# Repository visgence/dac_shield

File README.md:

Arduino DAC Shield
2013 Visgence Inc

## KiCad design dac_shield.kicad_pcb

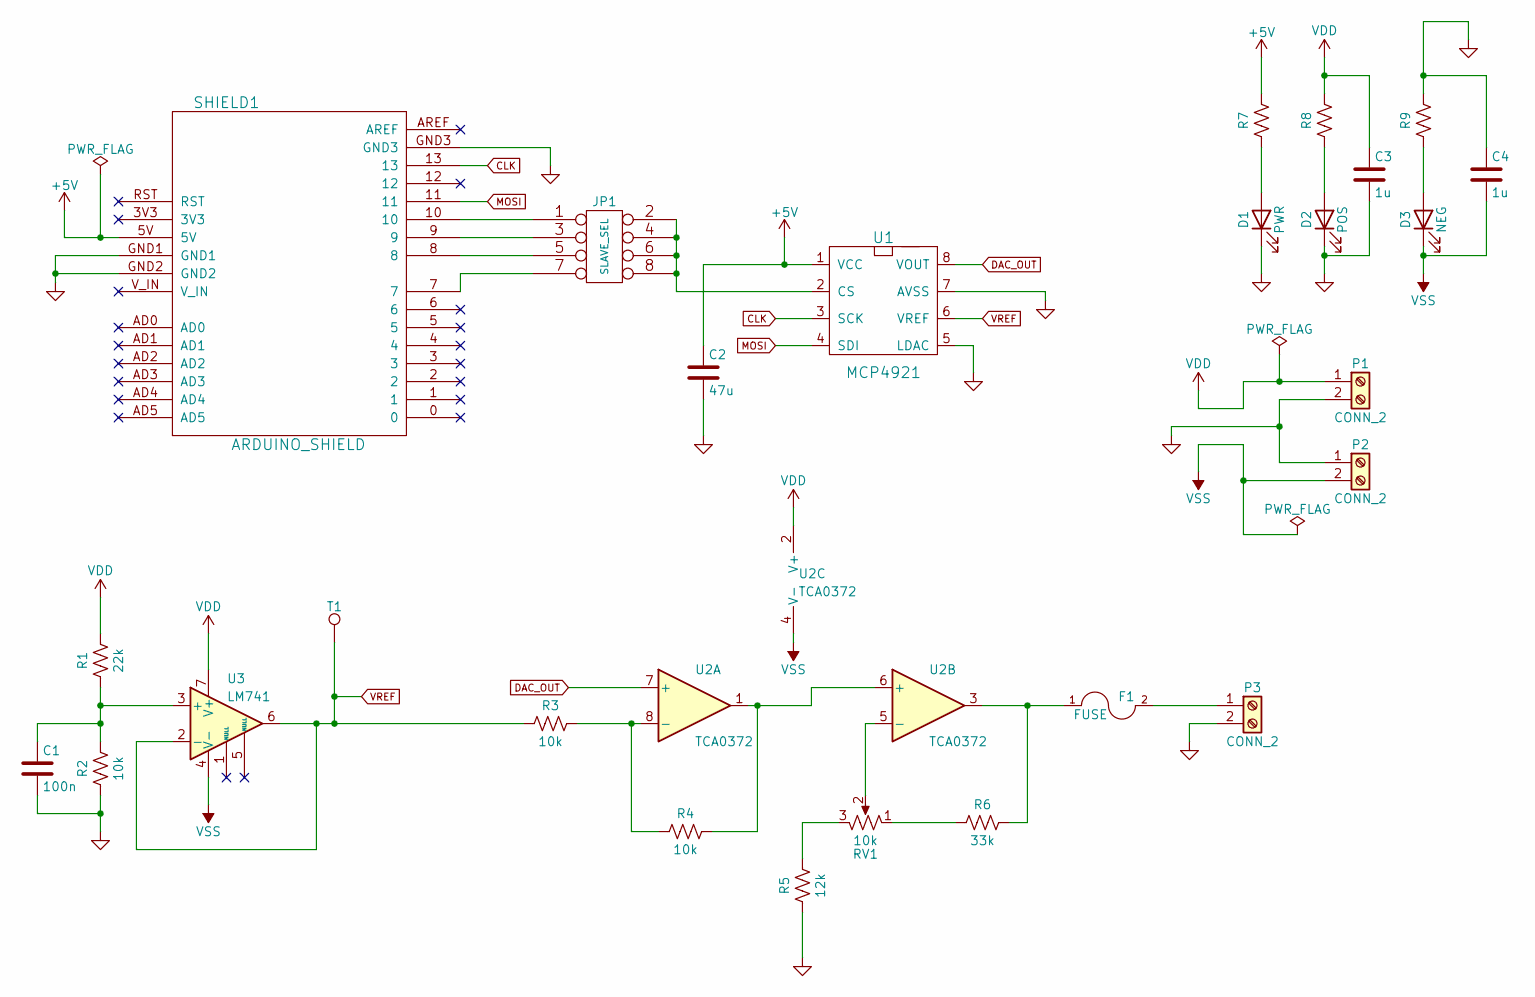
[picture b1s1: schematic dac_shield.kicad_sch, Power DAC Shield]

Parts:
C1: 100n; SM1206_VIS
C2: 47u; SM1206POL_VIS
C3, C4: 1u; SM1206_VIS
D1: PWR; LED_0603_1608Metric
D2: POS; LED_0603_1608Metric
D3: NEG; LED_0603_1608Metric
F1: FUSE; SM1210L
JP1: SLAVE_SEL; pin_array_4x2
P1, P2, P3: CONN_2; bornier2
R1: 22k; R_0603_1608Metric
R2, R3, R4: 10k; R_0603_1608Metric
R5: 12k; R_0603_1608Metric
R6: 33k; R_0603_1608Metric
R7, R8, R9: R_0603_1608Metric
RV1: 10k; Var_resistor
SHIELD1: ARDUINO_SHIELD; ARDUINO_SHIELD_2_040pins
T1: VrefTest; PINTST
U1: MCP4921; DIP-8__300_ELL
U2: TCA0372; DIP-8__300_ELL
U3: LM741; DIP-8__300_ELL

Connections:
+5V: C2.1, R7.2, SHIELD1.5V, U1.1 (VCC)
CLK: SHIELD1.13, U1.3 (SCK)
DAC_OUT: U1.8 (VOUT), U2.7 (+)
GND: C1.2, C2.2, C3.2, C4.1, D1.1 (K), D2.1 (K), P1.2, P2.1, P3.2, R2.1, R5.1, R9.2, SHIELD1.GND1, SHIELD1.GND2, SHIELD1.GND3, U1.5 (LDAC), U1.7 (AVSS)
MOSI: SHIELD1.11, U1.4 (SDI)
unnamed: C1.1, R1.1, R2.2, U3.3 (+)
unnamed: D1.2 (A), R7.1
unnamed: D2.2 (A), R8.1
unnamed: D3.2 (A), R9.1
unnamed: F1.1, R6.2, U2.3
unnamed: F1.2, P3.1
unnamed: JP1.1, SHIELD1.10
unnamed: JP1.2, JP1.4, JP1.6, JP1.8, U1.2 (CS)
unnamed: JP1.3, SHIELD1.9
unnamed: JP1.5, SHIELD1.8
unnamed: JP1.7, SHIELD1.7
unnamed: R3.2, R4.1, U2.8 (-)
unnamed: R4.2, U2.1, U2.6 (+)
unnamed: R5.2, RV1.3
unnamed: R6.1, RV1.1
unnamed: RV1.2, U2.5 (-)
VDD: C3.1, P1.1, R1.2, R8.2, U2.2 (V+), U3.7 (V+)
VREF: R3.1, T1.1, U1.6 (VREF), U3.2 (-), U3.6
VSS: C4.2, D3.1 (K), P2.2, U2.4 (V-), U3.4 (V-)

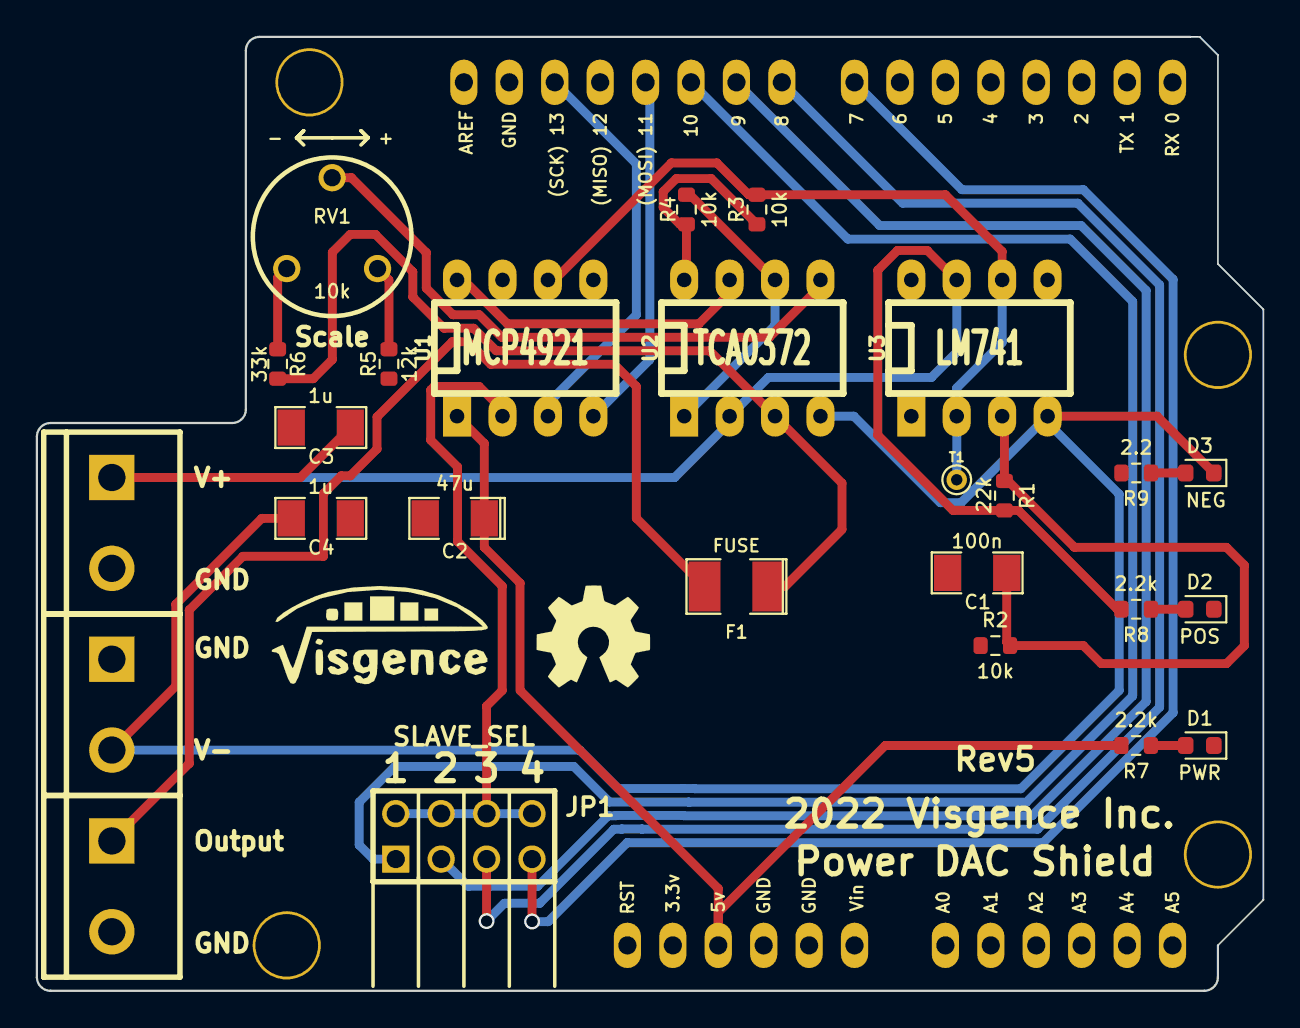
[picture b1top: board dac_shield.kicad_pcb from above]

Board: 2 copper layers, 68.6 x 53.3 mm, 33 parts (0 on the bottom side), 24 nets.

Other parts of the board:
G1: LOGO
G2: LOGO; OSHW_LOGO
h1, h2, h3, h4: pin; hole

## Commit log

2013-07-14 Inital Commit
2013-07-14 Added readme
2013-07-15 Started building the board
2013-07-15 some changes
2013-07-18 Added leds and caps
2013-07-18 Added new parts to board, created johnson connector
2013-07-18 Added logos, moved parts around
2013-07-23 Tied LDAC to GND, cleaned up silk screen
2013-07-23 Did first trial of routing
2013-07-30 Re-saved
2013-08-10 Added sample program to test dac shield
2013-08-11 resave
2013-08-11 Fixed problem with MCP4921 now showing up
2013-08-11 Added DAC back on board
2013-08-11 Added pinouts on silk screen
2013-08-11 Did first try at routing
2013-08-11 Had to move chip for more room, rerouted
2013-09-14 Added two shileds to mcp program
2013-09-14 Added demo for DAC
2013-09-21 Added fuse to output
2013-09-21 Changed resistors and caps to SMD
2013-09-21 Fixed non continous border
2013-09-21 Moved resistors to router easier
2013-09-21 First route and fill
2013-09-22 Changed fuse package, rerouted
2013-09-24 Silkscreen updates and routed
2013-11-24 Michaels modifications
2014-07-06 Added example program for arduino Mega
2014-07-23 Made rev4 changes
2014-08-16 Added easier examples, cleaned up code
2015-05-13 updates naming of slave select pins for clairty
2015-05-13 changes example to write to SS1
2015-05-23 adds slowSquare demo program
2015-05-23 removes .DS_Store
2015-05-23 adds basic .gitignore
2015-05-23 refactors simpleSquare to match simpleSine
2015-05-25 updates progmen definition for Arduino 1.5.7+, updates SSX definitions to match board silkscreen
2016-05-23 Added 3-D models and replaced parts on board.
2016-05-23 update model file references
2016-05-25 fixed LED and changed pot color
2016-06-02 adds a simple single-output program
2016-06-14 Changed origin to generate gerber files
2017-09-21 Changed to 2017
2022-04-04 fix compilation error on newer Arduino IDE
    https://forum.arduino.cc/t/error-when-compiling-prog_uchar-does-not-name-a-type/327741/2
2022-05-02 Added new project file
2022-05-02 Chaned all resistors
2022-05-02 Updated all power symbols
2022-05-02 Changed symbol for TCA0372
2022-05-02 Created custom-symbols to copy symbols with no replacement
2022-05-02 Removed all rescue symbols
2022-05-02 Re-mapping symbols to footprints
2022-05-02 Got PCB mostly updated
2022-05-02 Removed various symbols and footprint libs that have been updated
2022-05-02 Removed old style of project files
2022-05-02 Updated netlist
2022-05-02 Cleaning up tracks, updated led resistors
2022-05-02 Added curved traces, updated 3d settings
2022-07-22 Removed routing and copper fill
2022-07-22 very routed, note extra footprint warnings
